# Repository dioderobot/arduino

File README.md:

# PCB boards

This repository contains schematics and boards built using the `pcb` command line utility by Diode, using the Zener language and open source compiler

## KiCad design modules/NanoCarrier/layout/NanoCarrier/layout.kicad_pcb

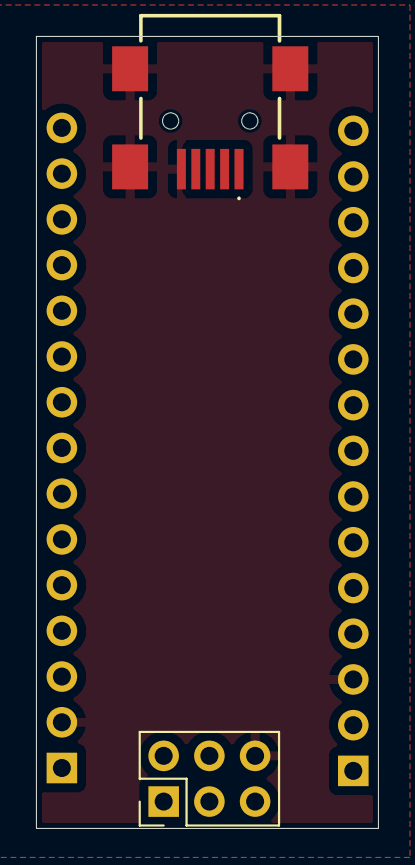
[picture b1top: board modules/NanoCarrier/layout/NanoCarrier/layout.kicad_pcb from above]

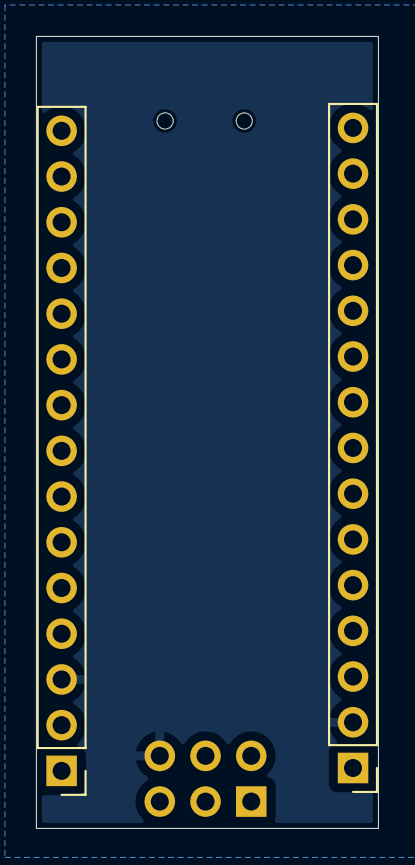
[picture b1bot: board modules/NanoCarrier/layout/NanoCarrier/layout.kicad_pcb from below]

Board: 4 copper layers, 19.0 x 44.0 mm, 4 parts (2 on the bottom side), 6 nets, no tracks yet.

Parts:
J1, J2: 2.54mm 15x1; PinHeader_1x15_P2.54mm_Vertical
J3: 10033526MN3212LF; 10033526N3212LF
J4: 2.54mm 3x2; PinHeader_2x03_P2.54mm_Vertical

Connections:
D11: J1.14, J4.4
D12: J1.15, J4.1
D13: J2.15, J4.3
GND: J1.3, J2.2, J3.5, J3.8, J3.9, J3.10, J3.11, J4.6
RESET: J1.2, J2.3, J4.5
VCC_5V: J2.4, J4.2

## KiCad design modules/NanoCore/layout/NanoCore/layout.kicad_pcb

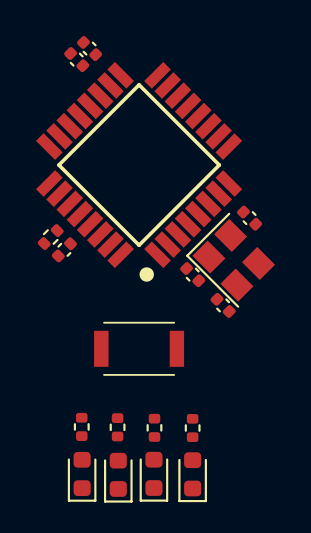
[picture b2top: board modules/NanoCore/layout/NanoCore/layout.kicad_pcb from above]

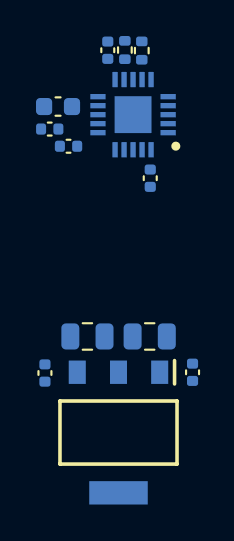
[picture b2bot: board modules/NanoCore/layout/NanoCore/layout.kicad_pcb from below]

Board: 4 copper layers, 31 parts (13 on the bottom side), 19 nets, no tracks yet.

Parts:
C1: 100nF; C_0402_1005Metric
C2, C3, C4, C11: 100nF 6.3V; C_0402_1005Metric
C5, C6: 22pF C0G; C_0402_1005Metric
C7: 10uF 25V; C_0805_2012Metric
C8: 100nF 25V; C_0402_1005Metric
C9: 22uF 10V; C_0805_2012Metric
C10, C12, C13, C14: 100nF 10V; C_0402_1005Metric
C15: 4.7uF 10V; C_0603_1608Metric
D1: LED YELLOW; LED_0603_1608Metric
D2, D3, D4: LED GREEN; LED_0603_1608Metric
IC1: ATMEGA328PMAU; QFP80P900X900X120-32N
IC2: AMS1117M5_0; SOT229P700X180-4N
IC3: FT231XQMR; QFN50P400X400X80-21N
R1: 10k 5%; R_0402_1005Metric
R2, R3: 1k 5%; R_0402_1005Metric
R4, R5: 470 5%; R_0402_1005Metric
R6, R7: 27 5%; R_0402_1005Metric
S1: SKRKAHE020; SKRKAEE020
Y1: 16MHz 18pF; Crystal_SMD_3225-4Pin_3.2x2.5mm

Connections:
D13: IC1.17, R2.1
DTR: C1.1, IC3.18
GND: C2.2, C3.2, C4.2, C5.2, C6.2, C7.2, C8.2, C9.2, C10.2, C11.2, C12.2, C13.2, C14.2, C15.2, D1.1, D2.1, IC1.3, IC1.5, IC1.21, IC2.1, IC2.4, IC3.3, IC3.13, IC3.21, S1.2, Y1.2, Y1.4
LED_L_ANODE: D1.2, R2.2
LED_PWR_ANODE: D2.2, R3.2
MCU.oscpair_XIN: C5.1, IC1.7, Y1.1
MCU.oscpair_XOUT: C6.1, IC1.8, Y1.3
RESET: C1.2, IC1.29, R1.1, S1.1
UART_RX: IC1.30, IC3.1
UART_TX: IC1.31, IC3.17
USB_SERIAL.CBUS0: D4.1, IC3.15
USB_SERIAL.CBUS1: D3.1, IC3.14
USB_SERIAL.P3V3OUT: C11.1, IC3.10
USB_SERIAL.RX_LED_ANODE: D3.2, R4.2
USB_SERIAL.TX_LED_ANODE: D4.2, R5.2
USB_SERIAL.USBDM_INTERNAL: IC3.9, R6.1
USB_SERIAL.USBDP_INTERNAL: IC3.8, R7.1
USB_VBUS: C7.1, C8.1, IC2.3
VCC_5V: C2.1, C3.1, C4.1, C9.1, C10.1, C12.1, C13.1, C14.1, C15.1, IC1.4, IC1.6, IC1.18, IC2.2, IC3.11, IC3.12, IC3.20, R1.2, R3.1, R4.1, R5.1

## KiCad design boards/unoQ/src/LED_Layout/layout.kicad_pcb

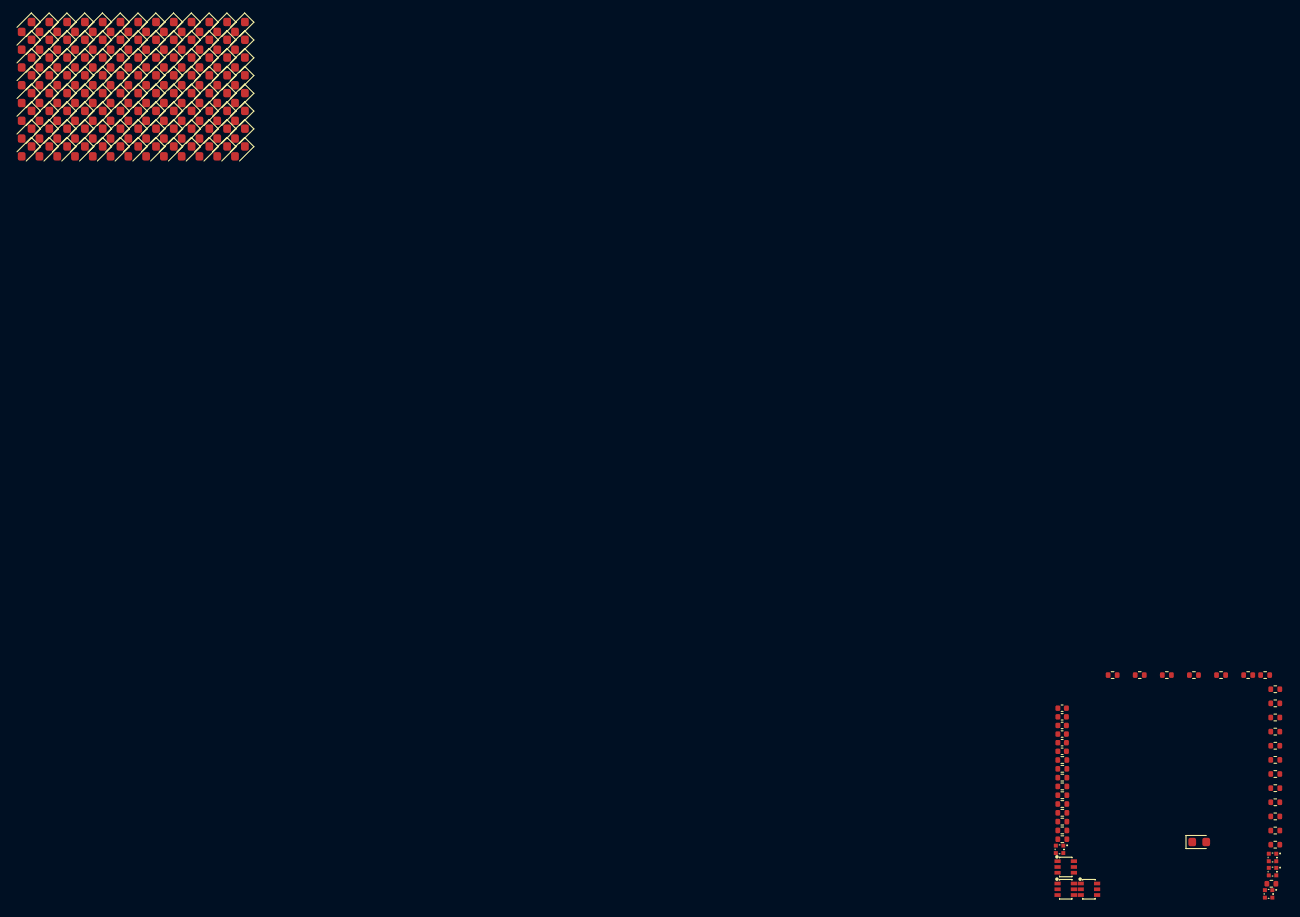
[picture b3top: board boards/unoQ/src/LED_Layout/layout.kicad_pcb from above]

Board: 2 copper layers, 148 parts (0 on the bottom side), 38 nets, no tracks yet.

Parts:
C1, C2, C3, C4, C5, C6: 100nF 10V; C_0402_1005Metric
D1, D2, D3, D4, D5, D6, D7, D8, D9, D10, D11, D12, D13, D14, D15, D16, D17, D18, D19, D20, D21, D22, D23, D24, D25, D26, D27, D28, D29, D30, D31, D32, D33, D34, D35, D36, D37, D38, D39, D40, D41, D42, D43, D44, D45, D46, D47, D48, D49, D50, D51, D52, D53, D54, D55, D56, D57, D58, D59, D60, D61, D62, D63, D64, D65, D66, D67, D68, D69, D70, D71, D72, D73, D74, D75, D76, D77, D78, D79, D80, D81, D82, D83, D84, D85, D86, D87, D88, D89, D90, D91, D92, D93, D94, D95, D96, D97, D98, D99, D100, D101, D102, D103, D104: LED BLUE; LED_0603_1608Metric
D105: LED GREEN; LED_0603_1608Metric
LED1, LED2, LED3, LED4: ?; LED-SMD_4P-L1.0-W1.0-TR_RGB
Q1, Q2, Q3: ?; SOT-363_L2.0-W1.3-P0.65-LS2.1-TL
R1, R2, R3, R4, R5, R6, R7, R8, R9, R10, R11: 22; R_0402_1005Metric
R12: 330; R_0402_1005Metric
R13, R14, R15, R16, R17, R18, R20, R22, R24, R26, R28, R30: 1.1k 1%; R_0402_1005Metric
R19, R21, R23, R25, R27, R29: 1k; R_0402_1005Metric

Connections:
GND: C1.2, C2.2, C3.2, C4.2, C5.2, C6.2, D105.1, Q1.1, Q1.4, Q2.1, Q2.4, Q3.1, Q3.4
LED_MATRIX_0_R: D1.2, D10.2, D11.1, D17.1, D19.2, D20.1, D28.2, D30.2, D31.1, D39.1, D43.2, D44.1, D58.2, D59.1, D72.2, D76.2, D77.1, D83.1, D96.2, D97.1, R1.2
LED_MATRIX_1_R: D1.1, D2.1, D12.2, D13.1, D17.2, D21.2, D22.1, D32.2, D33.1, D45.2, D46.1, D50.2, D60.2, D61.1, D62.1, D78.2, D79.1, D94.2, D98.2, D99.1, R2.2
LED_MATRIX_2_R: D8.2, D9.1, D14.2, D15.1, D23.2, D24.1, D28.1, D34.2, D35.1, D39.2, D47.2, D48.1, D50.1, D61.2, D63.2, D64.1, D80.2, D81.1, D100.2, D101.1, R4.2
LED_MATRIX_3_R: D2.2, D8.1, D9.2, D16.2, D18.1, D25.2, D26.1, D36.2, D37.1, D49.2, D51.1, D65.2, D66.1, D72.1, D82.2, D83.2, D84.1, D94.1, D102.2, D103.1, R5.2
LED_MATRIX_4_R: D3.1, D10.1, D11.2, D12.1, D13.2, D14.1, D15.2, D16.1, D18.2, D27.2, D29.1, D38.2, D40.1, D52.2, D53.1, D67.2, D68.1, D85.2, D86.1, D104.2, R6.2
LED_MATRIX_5_R: D4.2, D5.1, D19.1, D20.2, D21.1, D22.2, D23.1, D24.2, D25.1, D26.2, D27.1, D29.2, D41.2, D42.1, D54.2, D55.1, D69.2, D70.1, D87.2, D88.1, R7.2
LED_MATRIX_6_R: D6.2, D7.1, D30.1, D31.2, D32.1, D33.2, D34.1, D35.2, D36.1, D37.2, D38.1, D40.2, D41.1, D42.2, D56.2, D57.1, D71.2, D73.1, D89.2, D90.1, R8.2
LED_MATRIX_7_R: D43.1, D44.2, D45.1, D46.2, D47.1, D48.2, D49.1, D51.2, D52.1, D53.2, D54.1, D55.2, D56.1, D57.2, D74.2, D75.1, D91.2, D92.1, R9.2
LED_MATRIX_8_R: D58.1, D59.2, D60.1, D62.2, D63.1, D64.2, D65.1, D66.2, D67.1, D68.2, D69.1, D70.2, D71.1, D73.2, D74.1, D75.2, D93.2, D95.1, R10.2
LED_MATRIX_9_R: D76.1, D77.2, D78.1, D79.2, D80.1, D81.2, D82.1, D84.2, D85.1, D86.2, D87.1, D88.2, D89.1, D90.2, D91.1, D92.2, D93.1, D95.2, R11.2
LED_MATRIX_10_R: D3.2, D4.1, D5.2, D6.1, D7.2, D96.1, D97.2, D98.1, D99.2, D100.1, D101.2, D102.1, D103.2, D104.1, R3.2
LED_PWR: D105.2, R12.2
MCU_LED1_BLU_D: LED1.3, R13.1
MCU_LED1_GRN_D: LED1.4, R14.1
MCU_LED1_RED_D: LED1.2, R15.1
MCU_LED2_BLU_D: LED2.3, R16.1
MCU_LED2_GRN_D: LED2.4, R17.1
MCU_LED2_RED_D: LED2.2, R18.1
PWR_3P3V: LED1.1, LED2.1, LED3.1, LED4.1, R12.1
SOC_LED1_BLU_B: C1.1, Q2.2, R19.2
SOC_LED1_BLU_C: Q2.6, R20.2
SOC_LED1_BLU_D: LED3.3, R20.1
SOC_LED1_GRN_B: C2.1, Q1.5, R21.2
SOC_LED1_GRN_C: Q1.6, R22.2
SOC_LED1_GRN_D: LED3.4, R22.1
SOC_LED1_RED_B: C3.1, Q1.2, R23.2
SOC_LED1_RED_C: Q1.3, R24.2
SOC_LED1_RED_D: LED3.2, R24.1
SOC_LED2_BLU_B: C4.1, Q3.5, R25.2
SOC_LED2_BLU_C: Q3.3, R26.2
SOC_LED2_BLU_D: LED4.3, R26.1
SOC_LED2_GRN_B: C5.1, Q3.2, R27.2
SOC_LED2_GRN_C: Q3.6, R28.2
SOC_LED2_GRN_D: LED4.4, R28.1
SOC_LED2_RED_B: C6.1, Q2.5, R29.2
SOC_LED2_RED_C: Q2.3, R30.2
SOC_LED2_RED_D: LED4.2, R30.1

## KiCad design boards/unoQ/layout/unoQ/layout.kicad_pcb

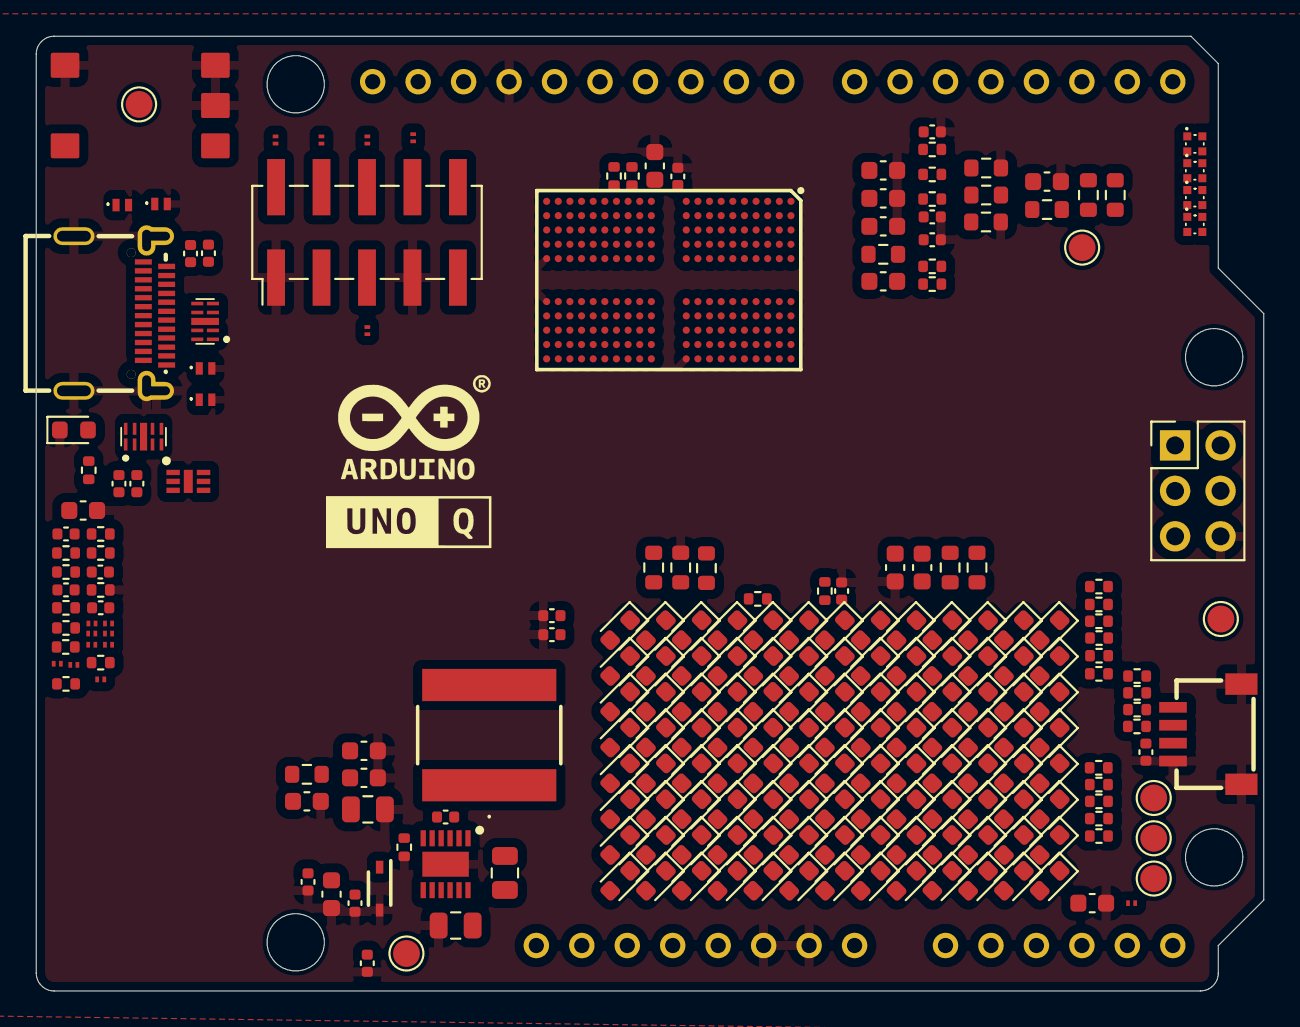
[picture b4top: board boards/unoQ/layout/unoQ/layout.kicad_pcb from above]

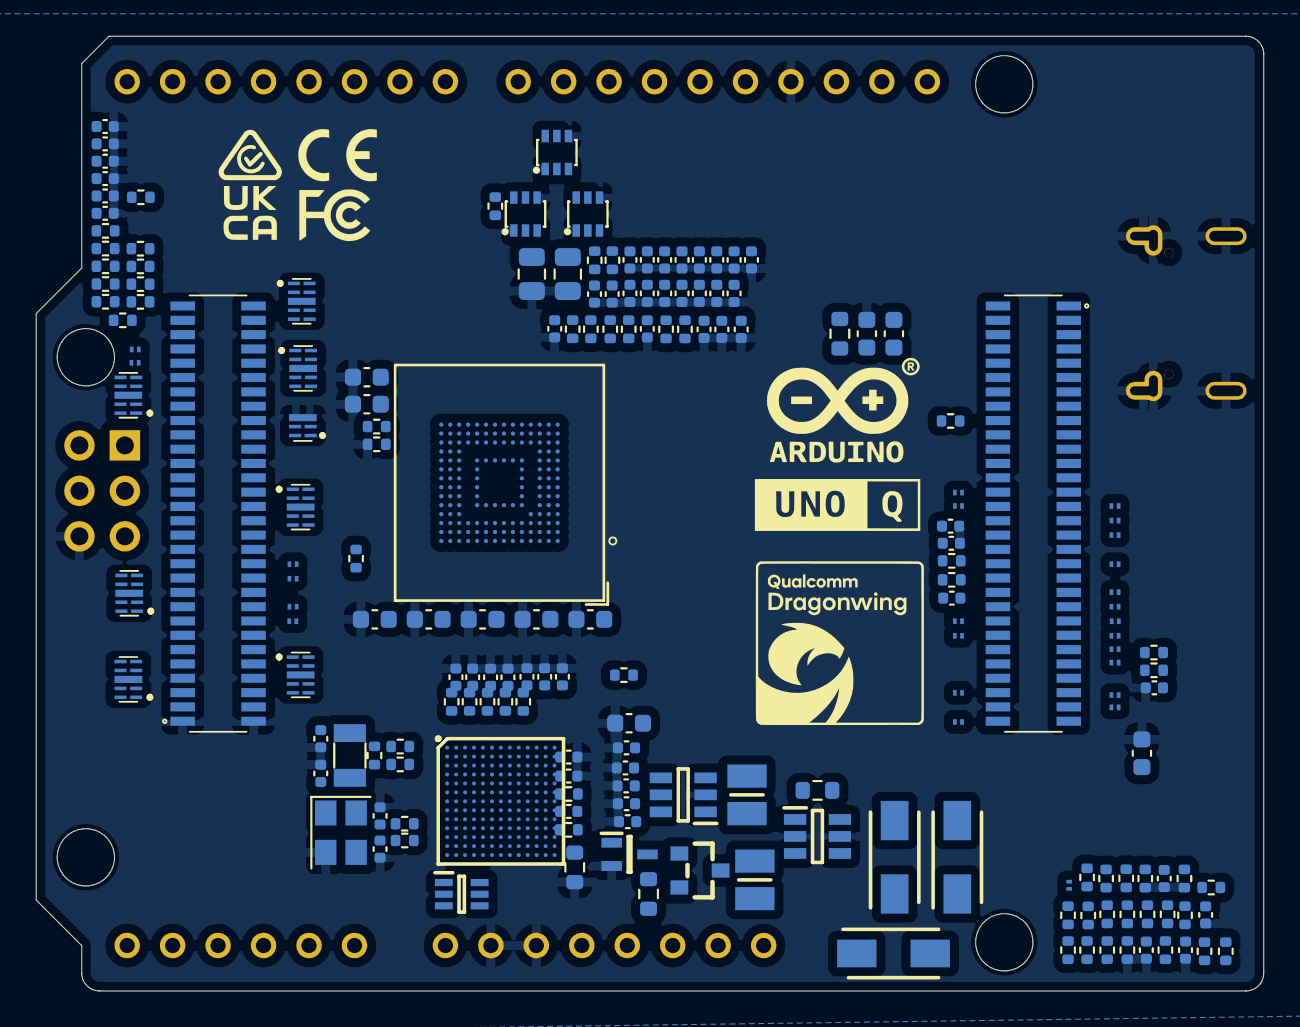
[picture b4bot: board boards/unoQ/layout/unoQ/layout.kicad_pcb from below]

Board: 4 copper layers, 68.6 x 53.3 mm, 424 parts (185 on the bottom side), 266 nets, no tracks yet.

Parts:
1: ?; 1571636-3
2: ?; 1X18-CUSTOM
C1: 100nF 16V; C_0402_1005Metric
C2: 22pF 50V; C_0603_1608Metric
C3, C4: 22uF 25V; C_0805_2012Metric
C5: 100nF 50V; C_0603_1608Metric
C6: 22uF 10V; C_0603_1608Metric
C7, C39, C40: 10uF 10V; C_0603_1608Metric
C8, C10: 120pF 25V; C_0603_1608Metric
C9, C15: 4.7uF 10V; C_0603_1608Metric
C11, C12: 22uF 6.3V; C_0603_1608Metric
C13, C103: 100nF 6.3V; C_0603_1608Metric
C14, C62: 4.7uF 6.3V; C_0805_2012Metric
C16, C99: 100nF 10V; C_0603_1608Metric
C17, C23, C32, C33, C34, C35, C41, C43, C44, C45, C46, C56, C70, C72, C74, C80, C81, C82, C83, C84, C85, C86, C87, C88, C89, C90, C91, C92, C93, C95, C97, C98: 100nF 6.3V; C_0402_1005Metric
C18, C19, C20: 100nF 50V; C_0402_1005Metric
C21, C22: 220pF 25V; C_0402_1005Metric
C24, C25, C26, C27, C28, C29, C30, C31: 330nF 10V; C_0402_1005Metric
C36, C37, C38, C42, C47, C48, C49, C50, C51, C52: 100nF 10V; C_0402_1005Metric
C53, C54, C55, C57, C58, C59, C60, C61, C63, C64, C65, C66, C67, C68, C69: 1uF 6.3V; C_0402_1005Metric
C71: 10uF 6.3V; C_0805_2012Metric
C73, C79, C100, C101: 1uF 6.3V; C_0603_1608Metric
C75, C76: 12pF 50V; C_0402_1005Metric
C77, C78: 7pF 25V; C_0402_1005Metric
C94, C96: 4.7uF 6.3V; C_0603_1608Metric
C102, C104, C105: 2.2uF 6.3V; C_0603_1608Metric
D1, D2, D3: SX34; DIOM5027X244N
D4: RCLAMP0522P.TCT; RCLAMP0522PTCT
D5, D6, D7, D8, D9, D10, D11, D12, D13, D14, D15, D16, D17, D18, D19, D20, D21, D22, D23, D24, D25, D26, D27, D28, D29, D30, D31, D32, D33, D34, D35, D36, D37, D38, D39, D40, D41, D42, D43, D44: DF2B7ASL; DF2S51ASLL3F
D45: PJGBLC24C; SODFL2512X90N
D46, D47, D48, D49, D50, D51, D52, D53, D54: RCLAMP0524PATCT
D55, D56, D57, D58: PESD5V0X1BL,315; PESD5V0S1BL315
D59, D60, D61, D62, D63, D64, D65, D66, D67, D68, D69, D70, D71, D72, D73, D74, D75, D76, D77, D78, D79, D80, D81, D82, D83, D84, D85, D86, D87, D88, D89, D90, D91, D92, D93, D94, D95, D96, D97, D98, D99, D100, D101, D102, D103, D104, D105, D106, D107, D108, D109, D110, D111, D112, D113, D114, D115, D116, D117, D118, D119, D120, D121, D122, D123, D124, D125, D126, D127, D128, D129, D130, D131, D132, D133, D134, D135, D136, D137, D138, D139, D140, D141, D142, D143, D144, D145, D146, D147, D148, D149, D150, D151, D152, D153, D154, D155, D156, D157, D158, D159, D160, D161, D162: LED BLUE; LED_0603_1608Metric
D163: LED GREEN; LED_0603_1608Metric
H1, H2, H3, H4: M3 ISO14580 Via; MountingHole_3.2mm_M3_ISO14580
IC1: LMR51440SDRRR; SON50P300X300X80-13N-D
IC2, IC3: TPS62A02APDDCR; SOT95P280X110-6N
IC4: RCLAMP3654PATCT; SON50P160X160X65-7N
IC5: MT53E512M32D1ZW-046 AUT:B; BGA200C65P12X22_1000X1450X105
IC6: 74LVC1G3157DW-7; SOT65P210X110-6N
IC7: STM32U585AII6TR; BGA169C50P13X13_700X700X60
J1, J2: CLE-130-01-G-DV-P-TR; CLE-130-01-X-DV-P-TR
J3: PinHeader_2x03_P2.54mm_Vertical
J4: PinHeader_2x05_P2.54mm_Vertical_SMD
JANALOG1: ?; 1X14-CUSTOM
L1, L2: TFM252012ALMA1R0MTAA; INDC2520X120N
L3: NRS8030T3R3MJGJ
LED1, LED2, LED3, LED4: ?; LED-SMD_4P-L1.0-W1.0-TR_RGB
Q1: SMMBT3904WT1G; SOT65P220X100-3N
Q2: ?; SOT-23_L2.9-W1.3-P1.90-LS2.4-BR
Q3, Q4, Q5: ?; SOT-363_L2.0-W1.3-P0.65-LS2.1-TL
R1: 301k 1%; R_0603_1608Metric
R2, R3, R15: 100k 1%; R_0603_1608Metric
R4: 1k 1%; R_0603_1608Metric
R5: 19.1k 1%; R_0603_1608Metric
R6, R19, R21, R23, R25, R27, R28, R29, R30, R31, R33, R35, R37, R39, R40, R41, R43, R45, R48, R49, R50, R51, R52, R53, R58, R59, R60, R61, R62, R63, R64, R65, R98, R99, R100, R101, R102, R103, R104, R105, R106, R108, R109, R110, R111: 0; R_0402_1005Metric
R7, R11, R12, R13, R18: 10k 1%; R_0603_1608Metric
R8, R16, R17: 0; R_0603_1608Metric
R9: 95.3k 1%; R_0603_1608Metric
R10: 499k 1%; R_0603_1608Metric
R14: 453k 1%; R_0603_1608Metric
R20, R22, R24, R26, R84, R86, R88, R90, R92, R94: 1k; R_0402_1005Metric
R32, R34, R36, R38, R47: 2.2k; R_0402_1005Metric
R42, R112: 100k; R_0402_1005Metric
R44, R46: 2.2; R_0402_1005Metric
R54, R55, R56, R57: 220k; R_0402_1005Metric
R66, R67, R68, R69, R70, R71, R72, R73, R74, R75, R76: 22; R_0402_1005Metric
R77: 330; R_0402_1005Metric
R78, R79, R80, R81, R82, R83, R85, R87, R89, R91, R93, R95: 1.1k 1%; R_0402_1005Metric
R96, R97: 240 1%; R_0402_1005Metric
R107: 1M; R_0402_1005Metric
R113, R114: 10k 1%; R_0402_1005Metric
TP1, TP2, TP3, TP4, TP5, TP6, TP7: Pad_D1.5mm; TestPoint_Pad_D1.5mm
U1: ?; CONN-SMD_4P-P1.00_CCSH-W10R-04TR-BK
U2: ?; BGA-153_L13.0-W11.5-P0.50-TL_KLM8G1GEME-B041
USB1: ?; USB-C-SMD_TYPE-C-24P-QT
Y1: 16MHz; Crystal_SMD_3225-4Pin_3.2x2.5mm
Y2: 32kHz; Crystal_SMD_3215-2Pin_3.2x1.5mm

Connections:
BUCK_5V_OUT: C6.1, C7.1, D2.2, L3.2, R3.1, R4.1
CCI_I2C_SCL0: R19.1, R20.1
CCI_I2C_SCL1: R21.1, R22.1
CCI_I2C_SDA0: R23.1, R24.1
CCI_I2C_SDA1: R25.1, R26.1
CSI0_A0_CLK_M: D4.1, D52.4, D52.7, J1.33
CSI0_A1_LN1_P: D52.2, D52.9, J1.29
CSI0_A2_LN2_M: D51.1, D51.10, J1.39
CSI0_B0_LN0_P: D49.5, D49.6, J1.23
CSI0_B1_LN1_M: D52.1, D52.10, J1.27
CSI0_C0_LN0_M: D49.4, D49.7, J1.21
CSI0_NC_CLK_P: D52.5, D52.6, J1.35
CSI1_A0_CLK_M: D4.2, J1.42
CSI1_A1_LN1_P: D48.5, D48.6, J1.46
CSI1_A2_LN2_M: D50.1, D50.10, J1.36
CSI1_B0_LN0_P: D48.2, D48.9, J1.52
CSI1_B1_LN1_M: D48.4, D48.7, J1.48
CSI1_B2_LN3_P: D50.5, D50.6, D51.5, D51.6, J1.28
CSI1_C0_LN0_M: D48.1, D48.10, J1.54
CSI1_C1_LN2_P: D50.2, D50.9, D51.2, D51.9, J1.34
CSI1_C2_LN3_M: D50.4, D50.7, D51.4, D51.7, J1.30
DC_DC.BUCK_5V_BOOT: C1.1, IC1.4
DC_DC.BUCK_5V_C: C3.2, C4.1
DC_DC.BUCK_5V_EN: IC1.9, R1.2, R2.1
DC_DC.BUCK_5V_FB: C2.2, IC1.7, R3.2, R5.1
DC_DC.BUCK_5V_FB_C: C2.1, R4.2
DC_DC.BUCK_5V_RT: IC1.6, R6.1
DC_DC.BUCK_5V_SW: C1.2, IC1.1, IC1.2, IC1.3, L3.1
DC_DC.BUCK_5V_VIN: C3.1, C5.1, D1.1, IC1.10, IC1.11, IC1.12, R1.1
DC_DC.LDO1_EN: IC2.1, R7.2, R8.1
DC_DC.LDO1_FB: C8.2, IC2.6, R9.1, R10.2
DC_DC.LDO1_LX: IC2.3, L2.1
DC_DC.LDO1_PG: C9.1, IC2.5, Q1.1, R11.1, R12.2
DC_DC.LDO2_EN: IC3.1, R13.2
DC_DC.LDO2_FB: C10.2, IC3.6, R14.2, R15.1
DC_DC.LDO2_LX: IC3.3, L1.1
DC_DC.USB_5V_VBUS_ON_N: Q1.3, Q2.1, R18.2
DC_IN: C18.1, C19.1, C20.1, D1.2, D45.1, J1.57, J1.59, JANALOG1.8
FORCED_USB_BOOT_N: D13.1, J4.2
GND: 1.3, 1.4, 1.5, 2.15, C4.2, C5.2, C6.2, C7.2, C9.2, C11.2, C12.2, C13.2, C14.2, C15.2, C16.2, C17.2, C18.2, C19.2, C20.2, C21.2, C22.2, C23.2, C32.2, C33.2, C34.2, C35.2, C36.2, C37.2, C38.2, C39.2, C40.2, C41.2, C42.2, C43.2, C44.2, C45.2, C46.2, C47.2, C48.2, C49.2, C50.2, C51.2, C52.2, C53.2, C54.2, C55.2, C56.2, C57.2, C58.2, C59.2, C60.2, C61.2, C62.2, C63.2, C64.2, C65.2, C66.2, C67.2, C68.2, C69.2, C70.2, C71.2, C72.2, C73.2, C74.2, C75.2, C76.2, C77.2, C78.2, C79.2, C80.2, C81.2, C82.2, C83.2, C84.2, C85.2, C86.2, C87.2, C88.2, C89.2, C90.2, C91.2, C92.2, C93.2, C94.2, C95.2, C96.2, C97.2, C98.2, C99.2, C100.2, C101.2, C102.2, C103.2, C104.2, C105.2, D4.3, D4.4, D5.2, D6.2, D7.2, D8.2, D9.2, D10.2, D11.2, D12.2, D13.2, D14.2, D15.2, D16.2, D17.2, D18.2, D19.2, D20.2, D21.2, D22.2, D23.2, D24.2, D25.2, D26.2, D27.2, D28.2, D29.2, D30.2, D31.2, D32.2, D33.2, D34.2, D35.2, D36.2, D37.2, D38.2, D39.2, D40.2, D41.2, D42.2, D43.2, D44.2, D45.2, D46.3, D46.8, D47.3, D47.8, D48.3, D48.8, D49.3, D49.8, D50.3, D50.8, D51.3, D51.8, D52.3, D52.8, D53.3, D53.8, D54.3, D54.8, D55.2, D56.2, D57.2, D58.2, D163.1, IC1.8, IC1.13, IC2.2, IC3.2, IC3.5, IC4.7, IC5.A3, IC5.A4, IC5.A9, IC5.A10, IC5.AB3, IC5.AB5, IC5.AB8, IC5.AB10, IC5.C1, IC5.C5, IC5.C8, IC5.C12, IC5.D2, IC5.D4, IC5.D9, IC5.D11, IC5.E1, IC5.E5, IC5.E8, IC5.E12, IC5.G1, IC5.G3, IC5.G5, IC5.G8, IC5.G10, IC5.G12, IC5.J1, IC5.J3, IC5.J10, IC5.J12, IC5.K2, IC5.K4, IC5.K9, IC5.K11, IC5.K12, IC5.N2, IC5.N4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
IO.CCI_I2C_SCL0_CONN: D7.1, J1.51, R19.2
IO.CCI_I2C_SCL1_CONN: D8.1, J1.24, R21.2
IO.CCI_I2C_SDA0_CONN: D9.1, J1.53, R23.2
IO.CCI_I2C_SDA1_CONN: D10.1, J1.22, R25.2
IO.EAR_M_R: C21.1, D11.1, J2.30, R27.2
IO.EAR_P_R: C22.1, D12.1, J2.28, R28.2
IO.HPH_L_CONN: D14.1, J2.36, R29.2
IO.HPH_REF_CONN: J2.40, R31.2
IO.HPH_R_CONN: D15.1, J2.38, R30.2
IO.LINEOUT_M_CONN: D16.1, J2.34, R40.2
IO.LINEOUT_P_CONN: D17.1, J2.32, R41.2
IO.MCU_I2C2_SCL_CONN: 2.18, R33.2
IO.MCU_I2C2_SDA_CONN: 2.17, R35.2
IO.MCU_I2C4_SCL_PD12_CONN: R37.2, U1.4
IO.MCU_I2C4_SCL_PF14_CONN: J2.16, R43.2
IO.MCU_I2C4_SDA_PD13_CONN: R39.2, U1.3
IO.MCU_I2C4_SDA_PF15_CONN: J2.18, R45.2
IO.MCU_SPI2_CLK_CONN: 2.14, R60.2
IO.MCU_SPI2_CLK_PD1_CONN: J3.3, R48.2
IO.MCU_SPI2_MISO_CONN: 2.13, R61.2
IO.MCU_SPI2_MISO_PC2_CONN: J3.1, R49.2
IO.MCU_SPI2_MOSI_CONN: 2.12, R62.2
IO.MCU_SPI2_MOSI_PC3_CONN: J3.4, R50.2
IO.MCU_SPI2_NSS_CONN: 2.11, R63.2
IO.MCU_USART1_RX_CONN: 2.1, R64.2
IO.MCU_USART1_TX_CONN: 2.2, R65.2
IO.MIC2_BIAS_CONN: D18.1, J2.33, R51.2
IO.MIC2_INN_CONN: D19.1, J2.31, R52.2
IO.MIC2_INP_CONN: D20.1, J2.29, R53.2
IO.MUX_SSRXN1_C: C24.1, D55.1, USB1.B10
IO.MUX_SSRXN2_C: C25.1, D46.5, D46.6, USB1.A10
IO.MUX_SSRXP1_C: C26.1, D56.1, USB1.B11
IO.MUX_SSRXP2_C: C27.1, D46.4, D46.7, USB1.A11
IO.MUX_SSTXN1_C: C28.1, D57.1, USB1.A3
IO.MUX_SSTXN2_C: C29.1, D46.1, D46.10, USB1.B3
IO.MUX_SSTXP1_C: C30.1, D58.1, USB1.A2
IO.MUX_SSTXP2_C: C31.1, D46.2, D46.9, USB1.B2
IO.SOC_CAM_MCLK0_R: D22.1, J1.16, R58.2
IO.SOC_CAM_MCLK1_R: D23.1, J1.18, R59.2
LED.LED_MATRIX_0_R: D59.2, D68.2, D69.1, D75.1, D77.2, D78.1, D86.2, D88.2, D89.1, D97.1, D101.2, D102.1, D116.2, D117.1, D130.2, D134.2, D135.1, D141.1, D154.2, D155.1, R66.2
LED.LED_MATRIX_1_R: D59.1, D60.1, D70.2, D71.1, D75.2, D79.2, D80.1, D90.2, D91.1, D103.2, D104.1, D108.2, D118.2, D119.1, D120.1, D136.2, D137.1, D152.2, D156.2, D157.1, R67.2
LED.LED_MATRIX_2_R: D66.2, D67.1, D72.2, D73.1, D81.2, D82.1, D86.1, D92.2, D93.1, D97.2, D105.2, D106.1, D108.1, D119.2, D121.2, D122.1, D138.2, D139.1, D158.2, D159.1, R69.2
LED.LED_MATRIX_3_R: D60.2, D66.1, D67.2, D74.2, D76.1, D83.2, D84.1, D94.2, D95.1, D107.2, D109.1, D123.2, D124.1, D130.1, D140.2, D141.2, D142.1, D152.1, D160.2, D161.1, R70.2
LED.LED_MATRIX_4_R: D61.1, D68.1, D69.2, D70.1, D71.2, D72.1, D73.2, D74.1, D76.2, D85.2, D87.1, D96.2, D98.1, D110.2, D111.1, D125.2, D126.1, D143.2, D144.1, D162.2, R71.2
LED.LED_MATRIX_5_R: D62.2, D63.1, D77.1, D78.2, D79.1, D80.2, D81.1, D82.2, D83.1, D84.2, D85.1, D87.2, D99.2, D100.1, D112.2, D113.1, D127.2, D128.1, D145.2, D146.1, R72.2
LED.LED_MATRIX_6_R: D64.2, D65.1, D88.1, D89.2, D90.1, D91.2, D92.1, D93.2, D94.1, D95.2, D96.1, D98.2, D99.1, D100.2, D114.2, D115.1, D129.2, D131.1, D147.2, D148.1, R73.2
LED.LED_MATRIX_7_R: D101.1, D102.2, D103.1, D104.2, D105.1, D106.2, D107.1, D109.2, D110.1, D111.2, D112.1, D113.2, D114.1, D115.2, D132.2, D133.1, D149.2, D150.1, R74.2
LED.LED_MATRIX_8_R: D116.1, D117.2, D118.1, D120.2, D121.1, D122.2, D123.1, D124.2, D125.1, D126.2, D127.1, D128.2, D129.1, D131.2, D132.1, D133.2, D151.2, D153.1, R75.2
LED.LED_MATRIX_9_R: D134.1, D135.2, D136.1, D137.2, D138.1, D139.2, D140.1, D142.2, D143.1, D144.2, D145.1, D146.2, D147.1, D148.2, D149.1, D150.2, D151.1, D153.2, R76.2
LED.LED_MATRIX_10_R: D61.2, D62.1, D63.2, D64.1, D65.2, D154.1, D155.2, D156.1, D157.2, D158.1, D159.2, D160.1, D161.2, D162.1, R68.2
LED.LED_PWR: D163.2, R77.2
LED.MCU_LED1_BLU_D: LED1.3, R78.1
LED.MCU_LED1_GRN_D: LED1.4, R79.1
LED.MCU_LED1_RED_D: LED1.2, R80.1
LED.MCU_LED2_BLU_D: LED2.3, R81.1
LED.MCU_LED2_GRN_D: LED2.4, R82.1
LED.MCU_LED2_RED_D: LED2.2, R83.1
LED.SOC_LED1_BLU_B: C47.1, Q4.2, R84.2
LED.SOC_LED1_BLU_C: Q4.6, R85.2
LED.SOC_LED1_BLU_D: LED3.3, R85.1
LED.SOC_LED1_GRN_B: C48.1, Q3.5, R86.2
LED.SOC_LED1_GRN_C: Q3.6, R87.2
LED.SOC_LED1_GRN_D: LED3.4, R87.1
LED.SOC_LED1_RED_B: C49.1, Q3.2, R88.2
LED.SOC_LED1_RED_C: Q3.3, R89.2
LED.SOC_LED1_RED_D: LED3.2, R89.1
LED.SOC_LED2_BLU_B: C50.1, Q5.5, R90.2
LED.SOC_LED2_BLU_C: Q5.3, R91.2
LED.SOC_LED2_BLU_D: LED4.3, R91.1
LED.SOC_LED2_GRN_B: C51.1, Q5.2, R92.2
LED.SOC_LED2_GRN_C: Q5.6, R93.2
LED.SOC_LED2_GRN_D: LED4.4, R93.1
LED.SOC_LED2_RED_B: C52.1, Q4.5, R94.2
LED.SOC_LED2_RED_C: Q4.3, R95.2
LED.SOC_LED2_RED_D: LED4.2, R95.1
LED_MATRIX_0: IC7.E2, R66.1
LED_MATRIX_1: IC7.F3, R67.1
LED_MATRIX_2: IC7.F4, R69.1
LED_MATRIX_3: IC7.G5, R70.1
LED_MATRIX_4: IC7.G6, R71.1
LED_MATRIX_5: IC7.G4, R72.1
LED_MATRIX_6: IC7.H6, R73.1
LED_MATRIX_7: IC7.G2, R74.1
LED_MATRIX_8: IC7.F1, R75.1
LED_MATRIX_9: IC7.G3, R76.1
LED_MATRIX_10: IC7.H4, R68.1
LPDDR4X.DRAM_ZQ0: IC5.A5, R96.1
LPDDR4X.DRAM_ZQ1: IC5.A8, R97.1
MCU.LED_MATRIX_11: IC7.M5, TP3.1
MCU.MCU_JTAG_TDI: IC7.A10, TP7.1
MCU.MCU_OSC32_IN_PC14: IC7.D1, R98.1
MCU.MCU_OSC32_OUT_PC15: IC7.E1, R99.1
MCU.MCU_OSC_IN_PH0_R: IC7.H1, R100.1
MCU.MCU_OSC_OUT_PH1_R: IC7.J1, R101.1
MCU.MCU_SOC_LPUART1_CTS: IC7.J9, R109.2
MCU.MCU_SOC_LPUART1_RTS: IC7.H10, R108.2
MCU.MCU_SOC_LPUART1_RX: IC7.H9, R111.2
MCU.MCU_SOC_LPUART1_TX: IC7.G8, R110.2
MCU.MCU_SPI3_CLK_R: IC7.A7, R102.2
MCU.MCU_SPI3_CS_N_R: IC7.E6, R103.2
MCU.MCU_SPI3_MISO_R: IC7.C7, R104.2
MCU.MCU_SPI3_MOSI_R: IC7.C6, R105.1
MCU.MCU_SPI3_RDY_R: IC7.N10, R106.2
MCU.MCU_VCAP: IC7.A4, IC7.N11
MCU.MCU_VREF_EN: IC6.6, IC7.M2, R112.1
MCU.OSC_16M_IN: C75.1, R100.2, Y1.1
MCU.OSC_16M_OUT: C76.1, R101.2, Y1.3
MCU.OSC_32K_IN: C77.1, R98.2, R107.1, Y2.1
MCU.OSC_32K_OUT: C78.1, R99.2, R107.2, Y2.2
MCU_BOOT0: IC7.C5, JANALOG1.1, R42.1, TP1.1
MCU_CRS_SYNC_PA10: IC7.F11, J2.25
MCU_I2C2_SCL: IC7.K9, R32.2, R33.1
MCU_I2C2_SDA: IC7.L9, R34.2, R35.1
MCU_I2C4_SCL_PD12: IC7.K10, R36.2, R37.1
MCU_I2C4_SCL_PF14: IC7.L6, R43.1, R44.2
MCU_I2C4_SDA_PD13: IC7.K12, R38.2, R39.1
MCU_I2C4_SDA_PF15: IC7.N6, R45.1, R46.2
MCU_JTAG_NJTRST_PB4: 2.9, IC7.B6, TP4.1
MCU_JTAG_SWCLK: IC7.C10, TP5.1
MCU_JTAG_SWDIO: IC7.F12, TP6.1
MCU_JTAG_SWO_PB3: 2.3, IC7.D6
MCU_LED1_BLU: IC7.B13, R78.2
MCU_LED1_GRN: IC7.D9, R79.2
MCU_LED1_RED: IC7.C13, R80.2
MCU_LED2_BLU: IC7.A13, R81.2
MCU_LED2_GRN: IC7.C11, R82.2
MCU_LED2_RED: IC7.C12, R83.2
MCU_MCO_PA8: IC7.G7, J2.23
MCU_NRST: IC7.H3, J3.5, JANALOG1.3, R47.1, TP2.1
MCU_OPAMP1_VINM_PA1: IC7.L3, J2.24
MCU_OPAMP1_VINP_PA0: IC7.K3, J2.22
MCU_OPAMP1_VOUT_PA3: IC7.N2, J2.20
MCU_PA4: IC7.N1, JANALOG1.9
MCU_PA5: IC7.K4, JANALOG1.10
MCU_PA6: IC7.N4, JANALOG1.11
MCU_PA7: IC7.J5, JANALOG1.12
MCU_PA11: 2.6, IC7.G13
MCU_PA12: 2.5, IC7.F13
MCU_PB0: 2.4, IC7.K5
MCU_PB1: 2.7, IC7.N5
MCU_PB2: 2.8, IC7.L5
MCU_PB8: 2.10, IC7.E5
MCU_PC0: IC7.J2, JANALOG1.14
MCU_PC1: IC7.J3, JANALOG1.13
MCU_PE7: IC7.L7, J2.12
MCU_PE8: IC7.K7, J2.14
MCU_PSSI_D0: IC7.H13, J2.1
MCU_PSSI_D1: IC7.G12, J2.3
MCU_PSSI_D2: IC7.G10, J2.5
MCU_PSSI_D3: IC7.G9, J2.7
MCU_PSSI_D4: IC7.C2, J2.9
MCU_PSSI_D5: IC7.B10, J2.11
MCU_PSSI_D6: IC7.A2, J2.13
MCU_PSSI_D7: IC7.C3, J2.15
MCU_PSSI_DE: IC7.L12, J2.21
MCU_PSSI_PDCK: IC7.L13, J2.17
MCU_PSSI_RDY: IC7.B3, J2.19
MCU_SDMMC1_CMD_PD2: IC7.F7, J2.2
MCU_SPI2_CLK: IC7.N13, R60.1
MCU_SPI2_CLK_PD1: IC7.F6, R48.1
MCU_SPI2_MISO: IC7.M12, R61.1
MCU_SPI2_MISO_PC2: IC7.J4, R49.1
MCU_SPI2_MOSI: IC7.L11, R62.1
MCU_SPI2_MOSI_PC3: IC7.K1, R50.1
MCU_SPI2_NSS: IC7.D5, R63.1
MCU_TRACE_CLK: IC7.A1, J2.4
MCU_TRACE_D0: IC7.D3, J2.6
MCU_TRACE_D2: IC7.D2, J2.8
MCU_TRACE_D3: IC7.E4, J2.10
MCU_USART1_RX: IC7.F5, R64.1
MCU_USART1_TX: IC7.B5, R65.1
MCU_VREFP: 2.16, C23.1, C73.1, C74.1, IC6.3, IC7.L1
MIPI_DSI0_CLK_M_CONN: D54.1, D54.10, J1.3
MIPI_DSI0_CLK_P_CONN: D54.2, D54.9, J1.5
MIPI_DSI0_L0_M_CONN: D53.1, D53.10, J1.12
MIPI_DSI0_L0_P_CONN: D53.2, D53.9, J1.10
MIPI_DSI0_L1_M_CONN: D53.4, D53.7, J1.6
MIPI_DSI0_L1_P_CONN: D53.5, D53.6, J1.4
MIPI_DSI0_L2_M_CONN: D54.4, D54.7, J1.9
MIPI_DSI0_L2_P_CONN: D54.5, D54.6, J1.11
MIPI_DSI0_L3_M_CONN: D49.1, D49.10, J1.15
MIPI_DSI0_L3_P_CONN: D49.2, D49.9, J1.17
MUX_SBU1_2: D47.1, D47.10, USB1.A8
MUX_SBU2_2: D47.2, D47.9, USB1.B8
MUX_SSRXN1_2: C24.2, R54.1
MUX_SSRXN2_2: C25.2, R55.1
MUX_SSRXP1_2: C26.2, R56.1
MUX_SSRXP2_2: C27.2, R57.1
PHONE_ON_N: 1.1, 1.2, C17.1, D5.1
PM_RESIN_N: D21.1, J4.8
PWR_3P3V: C10.1, C11.1, C32.1, C33.1, C34.1, C35.1, C72.1, C79.1, C80.1, C81.1, C82.1, C83.1, C84.1, C85.1, C86.1, C87.1, C88.1, C89.1, C90.1, C91.1, C92.1, C93.1, IC6.4, IC6.5, IC7.A3, IC7.A8, IC7.A11, IC7.B1, IC7.D13, IC7.E13, IC7.G1, IC7.J13, IC7.L2, IC7.N3, IC7.N7, IC7.N12, J1.58, J1.60, J2.53, J2.55, JANALOG1.2, JANALOG1.4, L1.2, LED1.1, LED2.1, LED3.1, LED4.1, R14.1, R16.2, R32.1, R34.1, R36.1, R38.1, R44.1, R46.1, R47.2, R77.1, U1.2
PWR_3P8V: C8.1, C12.1, C13.1, C14.1, IC3.4, L2.2, R10.1, R12.1, R13.1, R16.1, R17.1
SDC1_CMD: R113.2, U2.M5
SOC_GPIO18: D24.1, J2.49
SOC_GPIO28: D25.1, J2.51
SOC_GPIO_0_SE0: D26.1, J2.37
SOC_GPIO_1_SE0: D29.1, J2.39
SOC_GPIO_2_SE0: D30.1, J2.41
SOC_GPIO_3_SE0: D31.1, J2.43
SOC_GPIO_82_SE0: D32.1, J2.47
SOC_GPIO_86_SE0: D33.1, J2.45
SOC_GPIO_98: D34.1, J2.46
SOC_GPIO_99: D35.1, J2.48
SOC_GPIO_100: D27.1, J2.50
SOC_GPIO_101: D28.1, J2.52
SOC_UART_RX_SE4: D36.1, J4.6
SOC_UART_TX_SE4: D37.1, J4.4
SYS_5V: C15.1, C16.1, D2.1, D3.1, IC2.4, Q2.2, R7.1, R18.1
USB0_HS_DM_2: IC4.1, USB1.A7, USB1.B7
USB0_HS_DP_2: IC4.2, USB1.A6, USB1.B6
USB_5V_VBUS: C36.1, C37.1, C38.1, C39.1, C40.1, C42.1, D3.2, D6.1, D38.1, IC4.6, J2.54, J2.56, J3.2, JANALOG1.5, USB1.A4, USB1.A9, USB1.B4, USB1.B9
USB_CC1_2: D47.4, D47.7, USB1.A5
USB_CC2_2: D47.5, D47.6, USB1.B5
VBAT: C41.1, D39.1, J2.60, R17.2
VBUS_POWER_SWITCH_DISABLE_N: J4.10, R8.2
VCOIN: C43.1, C94.1, C95.1, D40.1, IC7.C1, J2.59
VOLUME_DOWN_N: D41.1, J4.3
VOLUME_UP_N: D42.1, J4.5
VREG_L2A_1P128V: C57.1, C58.1, C59.1, C60.1, C61.1, C62.1, IC5.AB4, IC5.AB9, IC5.F5, IC5.F8, IC5.G2, IC5.H1, IC5.H5, IC5.H8, IC5.H12, IC5.K1, IC5.K3, IC5.K10, IC5.N1, IC5.N3, IC5.N10, IC5.N12, IC5.R1, IC5.R5, IC5.R8, IC5.R12, IC5.T2, IC5.U5, IC5.U8
VREG_L3A_0P6V: C63.1, C64.1, C65.1, C66.1, C67.1, C68.1, C69.1, C70.1, C71.1, IC5.AA3, IC5.AA5, IC5.AA8, IC5.AA10, IC5.B3, IC5.B5, IC5.B8, IC5.B10, IC5.D1, IC5.D5, IC5.D8, IC5.D12, IC5.F3, IC5.F10, IC5.U3, IC5.U10, IC5.W1, IC5.W5, IC5.W8, IC5.W12, R96.2, R97.2
VREG_L14A_1P8V: C101.1, C102.1, U2.C6, U2.M4, U2.N4, U2.P3, U2.P5
VREG_L15A_1P8V: C44.1, C45.1, C46.1, C53.1, C54.1, C55.1, C56.1, C96.1, C97.1, C98.1, D43.1, D44.1, IC5.F1, IC5.F12, IC5.G4, IC5.G9, IC5.T4, IC5.T9, IC5.U1, IC5.U12, IC7.A6, IC7.H12, J2.57, J4.9, R20.2, R22.2, R24.2, R26.2, R113.1
VREG_L20A_2P96V: C103.1, C104.1, C105.1, U2.E6, U2.J10, U2.K9
eMMC.EMMC1_VDDI: C99.1, C100.1, U2.C2
eMMC.EMMC16G_WW28_GA01.NC: U2.A1, U2.A2, U2.A8, U2.A9, U2.A10, U2.A11, U2.A12, U2.A13, U2.A14, U2.B1, U2.B7, U2.B8, U2.B9, U2.B10, U2.B11, U2.B12, U2.B13, U2.B14, U2.C1, U2.C3, U2.C5, U2.C7, U2.C8, U2.C9, U2.C10, U2.C11, U2.C12, U2.C13, U2.C14, U2.D1, U2.D2, U2.D3, U2.D4, U2.D12, U2.D13, U2.D14, U2.E1, U2.E2, U2.E3, U2.E12, U2.E13, U2.E14, U2.F1, U2.F2, U2.F3, U2.F12, U2.F13, U2.F14, U2.G1, U2.G2, U2.G12, U2.G13, U2.G14, U2.H1, U2.H2, U2.H3, U2.H12, U2.H13, U2.H14, U2.J1, U2.J2, U2.J3, U2.J12, U2.J13, U2.J14, U2.K1, U2.K2, U2.K3, U2.K12, U2.K13, U2.K14, U2.L1, U2.L2, U2.L3, U2.L12, U2.L13, U2.L14, U2.M1, U2.M2, U2.M3, U2.M7, U2.M8, U2.M9, U2.M10, U2.M11, U2.M12, U2.M13, U2.M14, U2.N1, U2.N3, U2.N6, U2.N7, U2.N8, U2.N9, U2.N10, U2.N11, U2.N12, U2.N13, U2.N14, U2.P1, U2.P2, U2.P8, U2.P9, U2.P11, U2.P12, U2.P13, U2.P14
eMMC.NC: U2.A7, U2.E5, U2.F5, U2.G3, U2.K6, U2.K7, U2.P7, U2.P10

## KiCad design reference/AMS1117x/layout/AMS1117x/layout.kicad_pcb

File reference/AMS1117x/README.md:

# AMS1117x Linear Voltage Regulator

1A Low Dropout Linear Regulator with fixed 5.0V output for Arduino power supply.

## Usage

```starlark
AMS1117x = Module("//reference/AMS1117x/AMS1117x.zen")

AMS1117x(
    name = "REG_5V",
    add_led_indicator = True,     # Optional power LED
    VIN = Power("VIN"),           # 7-12V input (6.5-15V absolute max)
    VOUT = Power("5V"),           # Regulated 5V output
    GND = Ground("GND"),
)
```

## Features

- **AMS1117-5.0**: Fixed 5.0V output, 1A maximum current
- **Dropout**: 1.3V @ 1A load
- **Input Range**: 6.5V to 15V (7-12V recommended for Arduino)
- **Package**: SOT-223 with thermal tab
- **Protection**: Thermal shutdown, current limiting
- **Capacitors**: 10µF input + 22µF output for stability
- **Optional**: Power indicator LED

## Notes

- Minimum input voltage: 6.3V (5V + 1.3V dropout)
- Recommended input: 7-12V for proper thermal margin
- Output capacitor must be low-ESR (ceramic preferred)
- Tab pin must be soldered to ground plane for heat dissipation
- Maximum power dissipation: P = (VIN - VOUT) × IOUT
  - Example: (12V - 5V) × 1A = 7W (requires heatsinking!)
- For currents >500mA, ensure adequate copper area for cooling
- Input bypass capacitors should be placed close to VIN pin
- Optional LED draws ~3mA @ 5V

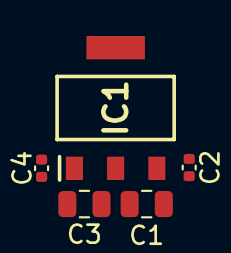
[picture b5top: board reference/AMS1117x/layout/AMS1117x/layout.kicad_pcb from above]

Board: 2 copper layers, 5 parts (0 on the bottom side), 3 nets, no tracks yet.

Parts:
C1: 10uF 25V; C_0805_2012Metric
C2: 100nF 25V; C_0402_1005Metric
C3: 22uF 10V; C_0805_2012Metric
C4: 100nF 10V; C_0402_1005Metric
IC1: AMS1117M5_0; SOT229P700X180-4N

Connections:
GND: C1.2, C2.2, C3.2, C4.2, IC1.1, IC1.4
VIN: C1.1, C2.1, IC1.3
VOUT_5V: C3.1, C4.1, IC1.2

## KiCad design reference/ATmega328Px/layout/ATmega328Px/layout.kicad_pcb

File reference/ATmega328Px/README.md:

# ATmega328Px Microcontroller

8-bit AVR microcontroller with 32KB Flash, 16MHz crystal, and Arduino bootloader compatibility.

## Usage

```starlark
ATmega328Px = Module("//reference/ATmega328Px/ATmega328Px.zen")

ATmega328Px(
    name = "mcu",
    VCC = Power("VCC"),           # 1.8V to 5.5V power supply
    GND = Ground("GND"),          # Ground
    UART = uart_interface,        # UART for serial communication
    SPI = spi_interface,          # SPI interface (CLK, MISO, MOSI, CS)
    I2C = i2c_interface,          # I2C interface (SDA, SCL)
    # Digital pins (optional)
    D2 = gpio_pin,
    D3 = pwm_pin,                 # PWM capable
    # ... D4 through D13
    # Analog pins (optional)
    A0 = adc_pin0,
    A1 = adc_pin1,
    # ... A2 through A7
)
```

## Features

- **ATmega328P-AU**: TQFP-32 package, 32KB Flash, 2KB SRAM, 1KB EEPROM
- **Clock**: 16MHz crystal with 22pF load capacitors
- **GPIO**: 23 programmable I/O pins
- **PWM**: 6 channels (D3, D5, D6, D9, D10, D11)
- **ADC**: 8 channels, 10-bit resolution
- **Interfaces**: UART, SPI, I2C
- **Power**: Complete decoupling with 100nF capacitors
- **Reset**: 10kΩ pull-up resistor, optional reset button

## Notes

- Crystal oscillator uses 22pF load capacitors for 18pF crystal
- AREF pin available as optional IO (can connect to external voltage reference)
- Reset pin pulled high through 10kΩ resistor
- Arduino bootloader compatible
- Operating voltage: 4.5-5.5V @ 16MHz (per datasheet)
- All power pins properly decoupled

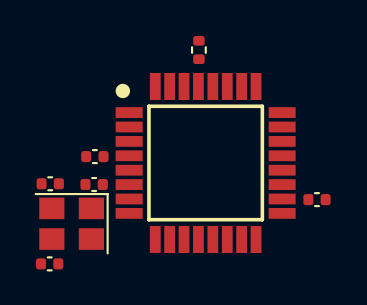
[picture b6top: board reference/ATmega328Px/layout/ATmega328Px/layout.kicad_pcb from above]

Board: 2 copper layers, 8 parts (0 on the bottom side), 5 nets, no tracks yet.

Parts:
C1, C2, C3: 100nF 6.3V; C_0402_1005Metric
C4, C5: 22pF C0G; C_0402_1005Metric
IC1: ATMEGA328PMAU; QFP80P900X900X120-32N
R1: 10k 5%; R_0402_1005Metric
Y1: 16MHz 18pF; Crystal_SMD_3225-4Pin_3.2x2.5mm

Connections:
GND: C1.2, C2.2, C3.2, C4.2, C5.2, IC1.3, IC1.5, IC1.21, Y1.2, Y1.4
RESET: IC1.29, R1.1
VCC: C1.1, C2.1, C3.1, IC1.4, IC1.6, IC1.18, R1.2
oscpair_XIN: C4.1, IC1.7, Y1.1
oscpair_XOUT: C5.1, IC1.8, Y1.3

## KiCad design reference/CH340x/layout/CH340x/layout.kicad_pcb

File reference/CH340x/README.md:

# CH340x USB to Serial Converter

USB to UART bridge IC for serial communication and Arduino programming.

## Usage

```starlark
CH340x = Module("//reference/CH340x/CH340x.zen")

CH340x(
    name = "usb_serial",
    add_tx_rx_leds = True,        # Optional TX/RX indicator LEDs
    VCC = Power("VCC"),           # 5V power supply
    USB_VCC = Power("USB_5V"),    # USB VBUS (can be same as VCC)
    GND = Ground("GND"),
    USB = usb_connector,          # USB 2.0 D+/D- differential pair
    UART = mcu_uart,              # UART interface to microcontroller
    DTR = reset_signal,           # DTR output for Arduino auto-reset
    RTS = rts_signal,             # RTS output (optional)
)
```

## Features

- **CH340G**: SOP-16 package USB to UART bridge
- **USB 2.0**: Full speed (12Mbps) with built-in termination
- **UART**: Up to 2Mbps baud rate
- **Clock**: 12MHz crystal oscillator
- **Regulator**: Built-in 3.3V regulator (V3 pin)
- **Signals**: DTR and RTS for Arduino auto-reset programming
- **Power**: 3.3V or 5V operation
- **Optional**: TX/RX indicator LEDs

## Arduino Auto-Reset

Connect DTR through 100nF capacitor to ATmega328P reset pin:

```starlark
# In your board design:
Capacitor(
    name = "C_AUTORESET",
    value = "100nF",
    package = "0402",
    P1 = usb_serial.DTR,
    P2 = mcu.RESET,
)
```

## Notes

- 12MHz crystal with 22pF load capacitors
- Built-in USB pull-up resistors (no external required)
- V3 pin provides 3.3V output for internal use
- R232 pin pulled high through 1kΩ resistor
- Compatible with Arduino IDE and avrdude
- Lower cost alternative to FTDI FT232RL
- Requires CH340 drivers (built into modern OS)
- TX/RX LEDs optional, add ~4mA current draw
- DTR/RTS are active-low signals

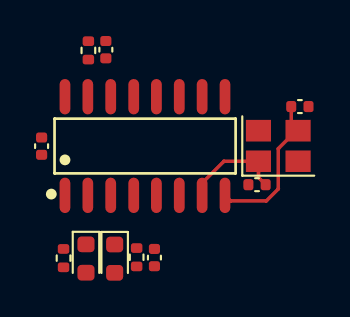
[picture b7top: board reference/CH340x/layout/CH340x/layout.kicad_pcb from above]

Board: 2 copper layers, 12 parts (0 on the bottom side), 11 nets.

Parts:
C1, C3: 100nF 10V; C_0402_1005Metric
C2: 100nF 6.3V; C_0402_1005Metric
C4, C5: 22pF C0G; C_0402_1005Metric
D1, D2: LED YELLOW; LED_0603_1608Metric
R1, R2, R3: 1k 5%; R_0402_1005Metric
U1: CH340G; SOIC-16_L9.9-W3.9-P1.27-LS6.0-BL
Y1: 12MHz 20pF; Crystal_SMD_3225-4Pin_3.2x2.5mm

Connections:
GND: C1.2, C2.2, C3.2, C4.2, C5.2, D1.1, U1.1, Y1.2, Y1.4
R232: R1.1, U1.15
RX_LED_ANODE: D1.2, R2.2
TX_LED_ANODE: D2.2, R3.2
UART_RX: D2.1, U1.3
UART_TX: R2.1, U1.2
USB_VCC: C1.1, U1.16
V3_INTERNAL: C2.1, U1.4
VCC: C3.1, R1.2, R3.1
oscpair_XIN: C4.1, U1.7, Y1.1
oscpair_XOUT: C5.1, U1.8, Y1.3
